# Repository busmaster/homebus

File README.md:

homebus
=======

home automation system

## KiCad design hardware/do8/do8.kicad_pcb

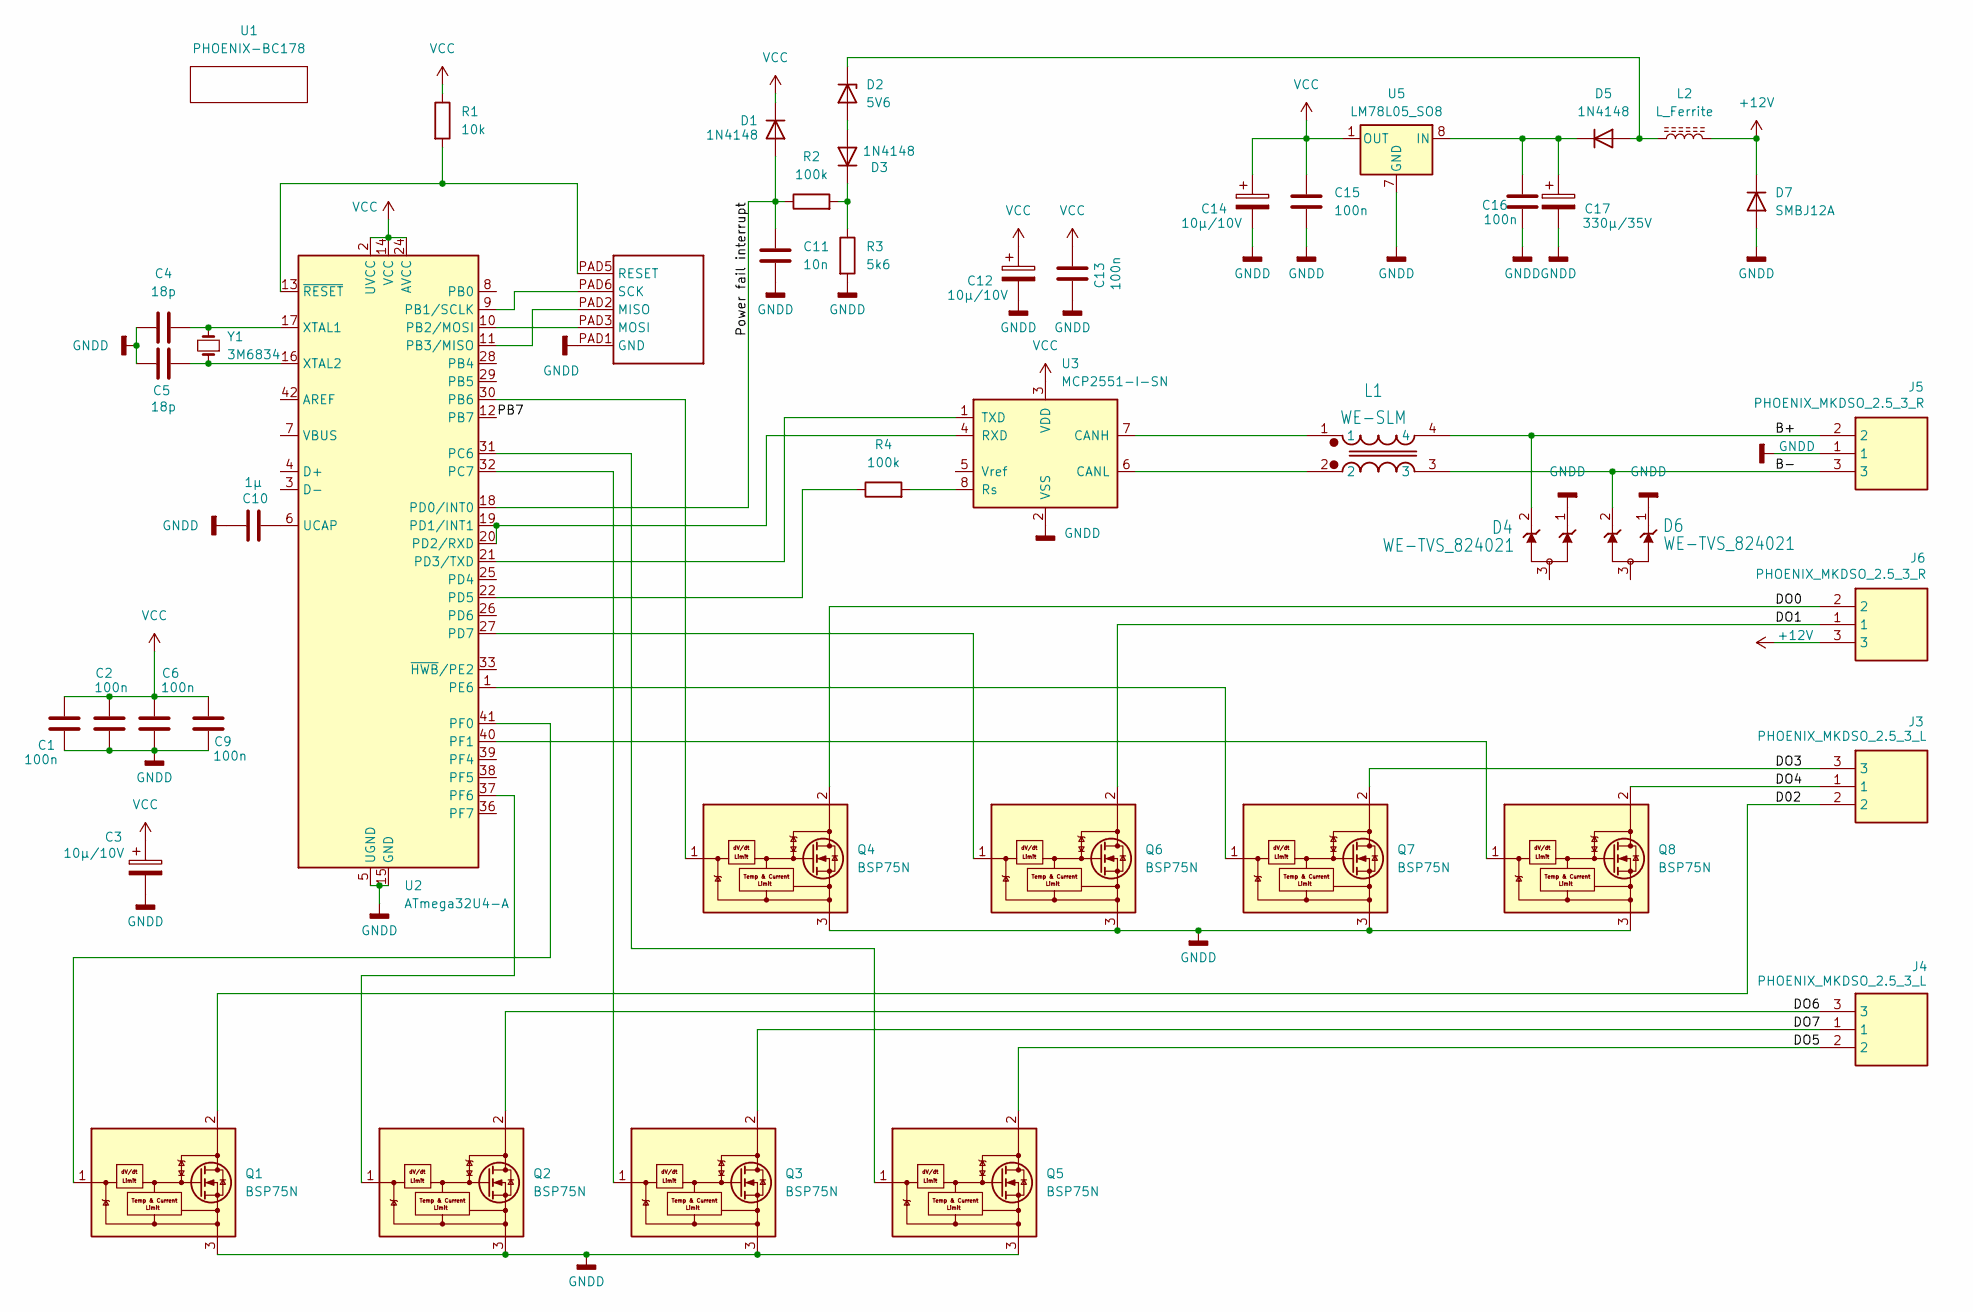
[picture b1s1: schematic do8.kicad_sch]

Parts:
C1, C2, C6, C9, C13, C15, C16: 100n; C_0603_1608Metric_Pad1.08x0.95mm_HandSolder
C3, C12, C14: 10µ/10V; CP_EIA-3216-18_Kemet-A_HandSolder
C4, C5: 18p; C_0603_1608Metric_Pad1.08x0.95mm_HandSolder
C10: 1µ; C_1206_3216Metric_Pad1.33x1.80mm_HandSolder
C11: 10n; C_0603_1608Metric_Pad1.08x0.95mm_HandSolder
C17: 330µ/35V; CP_Elec_10x10.5
D1, D3, D5: 1N4148; D_MiniMELF
D2: 5V6; D_MiniMELF
D4, D6: WE-TVS_824021
D7: SMBJ12A; D_SMB
J3, J4: PHOENIX_MKDSO_2.5_3_L; phoenix_mkdso_2.5_3_l; Manufacturer_Part_Number 2854102; Mouser Part Number 651-2854102
J5, J6: PHOENIX_MKDSO_2.5_3_R; phoenix_mkdso_2.5_3_r; Manufacturer_Part_Number 2854092; Mouser Part Number 651-2854092
L1: WE-SLM
L2: L_Ferrite; L_1806_4516Metric
Q1, Q2, Q3, Q4, Q5, Q6, Q7, Q8: BSP75N; SOT-223
R1: 10k; R_0603_1608Metric_Pad0.98x0.95mm_HandSolder
R2, R4: 100k; R_0603_1608Metric_Pad0.98x0.95mm_HandSolder
R3: 5k6; R_0603_1608Metric_Pad0.98x0.95mm_HandSolder
T1: atmel-isp
U1: PHOENIX-BC178; phoenix-bc178-reduced-3
U2: ATmega32U4-A; TQFP-44_10x10mm_P0.8mm
U3: MCP2551-I-SN; SOIC-8_3.9x4.9mm_P1.27mm
U5: LM78L05_SO8; SOIC-8_3.9x4.9mm_P1.27mm
Y1: 3M6834; Crystal_SMD_HC49-SD

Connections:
+12V: D7.1 (K), J6.3, L2.2
/B+: D4.2, J5.2, L1.4
/B-: D6.2, J5.3, L1.3
/D02: J3.2, Q1.2 (DRAIN)
/DO0: J6.2, Q4.2 (DRAIN)
/DO1: J6.1, Q6.2 (DRAIN)
/DO3: J3.3, Q7.2 (DRAIN)
/DO4: J3.1, Q8.2 (DRAIN)
/DO5: J4.2, Q5.2 (DRAIN)
/DO6: J4.3, Q2.2 (DRAIN)
/DO7: J4.1, Q3.2 (DRAIN)
/Power fail interrupt: C11.1, D1.2 (A), R2.1, U2.18 (PD0)
GNDD: C1.1, C2.1, C3.2, C4.1, C5.1, C6.1, C9.1, C10.2, C11.2, C12.2, C13.1, C14.2, C15.2, C16.2, C17.2, D4.1, D6.1, D7.2 (A), J5.1, Q1.3 (SOURCE), Q1.4 (SOURCE), Q2.3 (SOURCE), Q2.4 (SOURCE), Q3.3 (SOURCE), Q3.4 (SOURCE), Q4.3 (SOURCE), Q4.4 (SOURCE), Q5.3 (SOURCE), Q5.4 (SOURCE), Q6.3 (SOURCE), Q6.4 (SOURCE), Q7.3 (SOURCE), Q7.4 (SOURCE), Q8.3 (SOURCE), Q8.4 (SOURCE), R3.2, T1.PAD1 (GND), U2.5 (UGND), U2.15 (GND), U2.23 (GND), U2.35 (GND), U2.43 (GND), U3.2 (VSS), U5.2 (GND), U5.3 (GND), U5.6 (GND), U5.7 (GND)
unnamed: D2.2 (A), D3.2 (A)
unnamed: D2.1 (K), D5.2 (A), L2.1
unnamed: D3.1 (K), R2.2, R3.1
unnamed: C16.1, C17.1, D5.1 (K), U5.8 (IN)
unnamed: Q1.1 (IN), U2.41 (PF0)
unnamed: Q2.1 (IN), U2.37 (PF6)
unnamed: Q3.1 (IN), U2.32 (PC7)
unnamed: Q4.1 (IN), U2.30 (PB6)
unnamed: Q5.1 (IN), U2.31 (PC6)
unnamed: Q6.1 (IN), U2.27 (PD7)
unnamed: Q7.1 (IN), U2.1 (PE6)
unnamed: Q8.1 (IN), U2.40 (PF1)
unnamed: T1.PAD2 (MISO), U2.11 (PB3)
unnamed: T1.PAD3 (MOSI), U2.10 (PB2)
unnamed: R1.2, T1.PAD5 (RESET), U2.13 (~RESET)
unnamed: T1.PAD6 (SCK), U2.9 (PB1)
unnamed: U2.19 (PD1), U2.20 (PD2), U3.4 (RXD)
unnamed: U2.21 (PD3), U3.1 (TXD)
unnamed: R4.1, U2.22 (PD5)
unnamed: C10.1, U2.6 (UCAP)
unnamed: C4.2, U2.17 (XTAL1), Y1.2
unnamed: C5.2, U2.16 (XTAL2), Y1.1
unnamed: L1.1, U3.7 (CANH)
unnamed: L1.2, U3.6 (CANL)
unnamed: R4.2, U3.8 (Rs)
VCC: C1.2, C2.2, C3.1, C6.2, C9.2, C12.1, C13.2, C14.1, C15.1, D1.1 (K), R1.1, U2.2 (UVCC), U2.14 (VCC), U2.24 (AVCC), U2.34 (VCC), U2.44 (AVCC), U3.3 (VDD), U5.1 (OUT)

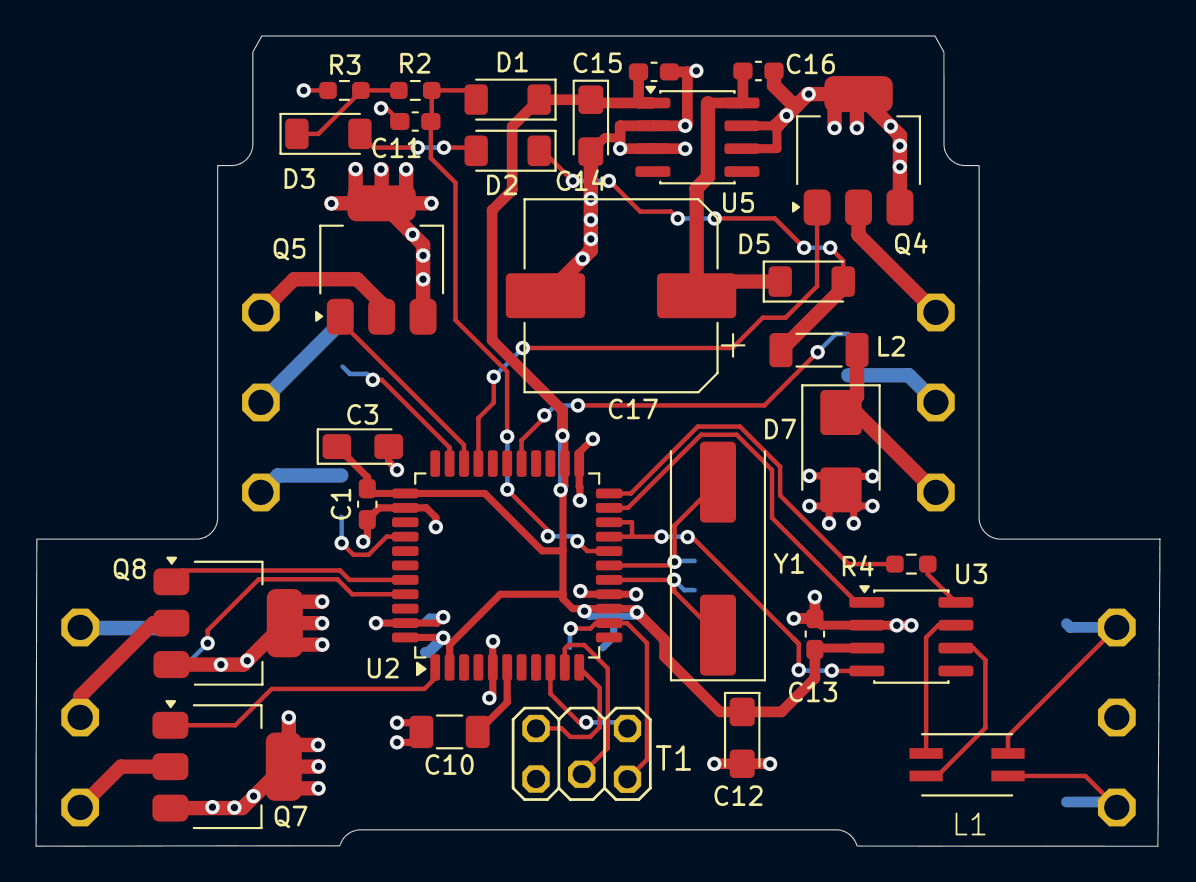
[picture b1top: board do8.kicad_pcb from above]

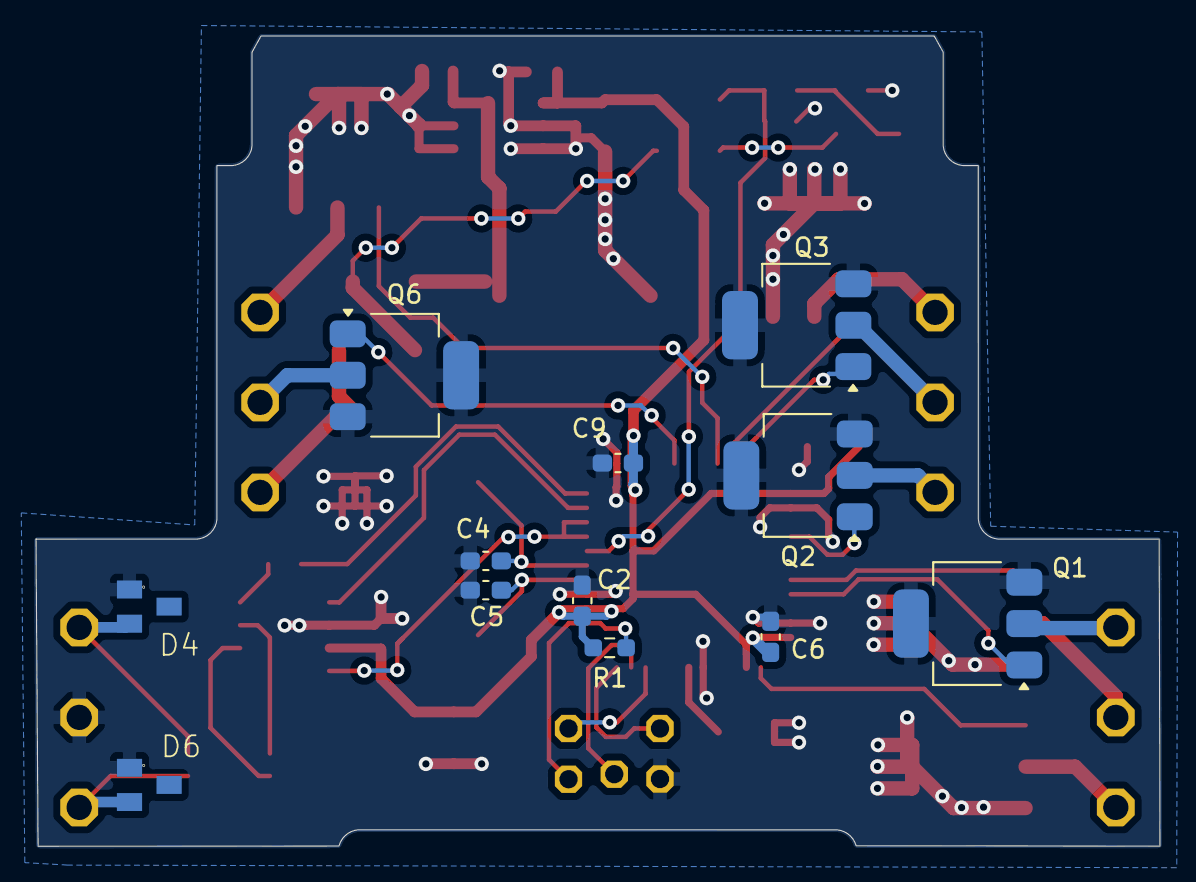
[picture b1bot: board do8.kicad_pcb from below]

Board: 2 copper layers, 62.4 x 45.0 mm, 46 parts (12 on the bottom side), 39 nets.

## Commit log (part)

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2015-11-28 status led integration
2015-11-29 allow client pty while sio device is not yet available
2015-12-01 mega88 clock calibration
2015-12-05 correction of build directory path
2016-01-25 new bus telegram types for clock calibration
2016-01-25 clock calibration
2016-01-25 clock calibraton firmware for atmega88 based devices
2016-02-01 sio send lockup
2016-02-01 change of manufacturer and product string
2016-02-09 sio driver reports one received character on startup
2016-02-09 file mode changes
2016-02-11 Update README
    Test2
2016-02-19 elko position move
2016-02-23 bootloader for rs485if
2016-02-25 Fix usage message in eventmonitor and monitor
2016-02-29 firmwareupdate doesn't start due to buffered rx frames in sio device
2016-02-29 adapt file mode
2016-02-29 remove debug sio support
2016-02-29 prepare usage of siosingle
2016-03-08 removed bit offset undefs for m128 (moved to sio_c.h)
2016-03-08 version 1.05 (use of siosingle)
2016-03-08 use of siosingle for switchv2
2016-03-08 preparation for siosingle usage at do31 and rs485if
2016-03-13 board specific modules for rs485if
2016-03-15 atmega1284 adaptions
2016-03-19 dmx test
2016-03-19 correction of BUS_TRANSCEIVER_POWER_UP macro
2016-03-19 part value actualization
2016-03-19 set unix line termination
2016-03-20 port settings
2016-04-10 doc for initial flash setup
2016-04-10 correction of programming steps
2016-05-09 change actval from max wind to current wind
2016-05-16 auto switch off for lamp in garage and bathroom
2016-05-30 read command from stdin to terminate process
2016-05-30 correction of select rfds setup
2016-06-27 New window for kitchen. Support addition kitchen lamp.
2016-06-27 new window for kitchen
2016-09-18 change of socket_1 relais connection from NO to NC
2016-09-18 add support for 14.7456MHz and 1.8432MHz clock
2016-09-18 hardware design pwm4
2016-09-19 new command: generate a switch event
2016-09-21 set default own address in server mode
2016-09-21 set default own address in server mode to command line parameter
2016-09-21 converted to unix line termination
2016-09-21 setup window for disabling the doorbell
2016-10-01 changed crystal frequency
2016-10-01 add support for rs485if and pwm4 devices
2016-10-03 initial version of pwm4 application
2016-10-03 missing file
2016-10-03 rs485 test
2016-10-03 support for rs485f and pwm4
2016-10-10 reduce flash usage by sio tx simplification
2016-10-15 support rs485if and pwm4 actval
2016-10-15 optocoupler input and output resistor change
2016-10-17 output restore on power on
2016-10-17 unix line termination
2016-10-17 pwm for switch 46
2016-10-25 new command inforange for bus scan
2016-10-30 enable pullup on all input pins
2016-12-14 missing header
2017-01-03 save max wind value to eeprom
2017-01-03 rearrangement of buttons
2017-01-03 file mode
2017-01-04 sleep before flushing the sio input on startup
2017-01-17 use siosingle
2017-01-31 pwm4: set pwm frequency to 900 Hz from 225 Hz
    This high frequency is required due to instability of the used power supply
    (Meanwell LRS-50-24).
2017-01-31 pwm4 sio: support for additional cpu clocks
2017-02-18 eventmonitor: support device type PWM4
2017-02-27 removed debug print
2017-02-28 pwm: extension of interface: separate function for on/off
2017-02-28 sio: support EVEN parity
2017-02-28 pwm4 application: use extended pwm interface
2017-02-28 smartmeter tool: use EVEN parity
2017-02-28 new hardware: smartmeter interface
2017-03-14 smartmeterif: initial debug version
2017-03-18 smartmeter support
2017-03-18 pwm4: renaming mask -> set
2017-03-19 add new telegram type for diag data
2017-03-19 monitor: add support for diag telegram
2017-04-04 pwm4 application: delayed switch off of the common power supply
2017-04-04 smartmeterif hardware: value changes
2017-05-07 change \r\n to \n
2017-05-07 fflush stdout
2017-05-09 visu: reduce code duplication
2017-05-13 modulservice: check receiver address
2017-05-24 tools: mqtt: initial demo version
2017-06-04 mqtt: test
2017-06-04 tools: mqtt: pasre command line params
2017-06-05 tools: eventmonitor: optional listen only mode
2017-06-05 tools: mqtt: parameter for event listen address
2017-06-05 do31: eBusDevReqSetClientAddr does not work
2017-06-19 pwm4: unable to switch on after power fail
2017-06-20 tools: mqtt: subscriber support for do31 shader
2017-07-02 tools: mqtt: command line parameter for broker address/port
2017-07-02 tools: mqtt: debian init script example
2017-07-11 tools: mqtt: wait for response on DO31 ReqSetValue
2017-07-11 usbif: use siosingle
2017-07-15 tools: bottongpio: initial version
2017-07-15 tools: buttongpio: wrong telegram processing
2017-07-16 tool: mqtt: extend example configuration
2017-07-22 tools: mqtt: add lights stairs
2017-07-25 tools: modulservice: support changed pwm4 actval protocol
2017-07-25 pwm4: wrong actval state
2017-07-29 tools: mqtt: add PWM4 support
2017-08-09 tools: mqtt: sw8 device support
2017-10-17 buttongpio: trigger on swtichstate additionally
2017-10-31 switchv2a: replace switchState by actualValue telegrams
2017-10-31 project241: use eDigOut30 for door light
2017-11-07 bus: introduction gettime/settime telegram types
2017-11-11 application240: door light auto/on/off
2017-11-11 mqtt: topic extension
2017-11-12 buttongpio: add supoort for eBusDevReqActualValueEvent/sw8 telegram
2017-11-20 visu: implement ButtonBackPressed to call dialog's hide methode
2017-11-20 visu: support mjpeg camera
2017-11-26 visu: auto mode for door light
2017-11-27 visu: remove moduleservice debug prints
2017-11-28 visu: smartmeter support
2017-12-05 added .gitignore
2017-12-05 visu: do not smartmeter from startup
2017-12-11 add missing files
2017-12-11 add hardware
2018-02-24 monitor: support eBusDevTypeSmIf
2018-02-24 change to unix line ending
2018-02-25 switchv2_garage: optimize for size
2018-02-25 switchv2_luminance: optimize for size
2018-02-25 monitor: add setvar/getvar support
2018-02-25 monitor: output format cleanup
2018-04-03 bus: busvar support
2018-04-03 monitor: use variable for compiler options
2018-04-03 monitor: add setvar/getvar result code
2018-04-07 busvar: change index type to uint8_t from uint16_t
2018-04-08 monitor: wrong usage help for option logfile
2018-05-12 busvar: stabilisation
2018-06-26 busvar: make variable value peristent to eeprom optionally
2018-06-26 klaus240: use siosingle
2018-07-28 tools: initial varserver
2018-09-22 bustest: correction of library dependency order
2018-10-08 bus: pwm16 protocol support
2019-01-19 sonoff_socket: initial version
2019-10-30 sw88 1.06 hAT
2019-10-30 Anpassungen
2019-10-30 gitignore
2019-10-30 Hardwarelayouts
2019-10-30 Bootloader
2019-10-30 pwm16
2019-10-30 Projekt hinzugefügt
2019-10-30 missing makefile
2019-10-30 Eagle Files pwm16 added
2019-11-01 Portserver für Webapp
2019-11-07 spelling error
2019-11-08 tasttimeout
2019-11-25 do31: set reset state of interrupt mask registers
    The bootloader might leave interrupt mask register settings that
    can trigger unexcepted interrupts. These unexpected interrupt are
    handled by the default handler that calls the reset handler.
2020-05-03 mqtt: support sw8 input actval event
    On publishing mqtt sw8 input events a bus actval event is generated:
    mosq_publish ... -t home/eingang/bewegungsmelder/set -m 1
    -> bus actval event to all receivers from the configuration receiver option
    -> mqtt publish home/eingang/bewegungsmelder/actual
    The configuration has to be extended by the receiver option, e.g.:
    - topic: home/eingang/bewegungsmelder
2020-05-24 busvar: whitespace cleanup
2020-05-29 mqtt: add bus variable support
    bus device sends ReqSetVar to mqtt -> publish variable actual value
    publish variable set value to mqtt -> ReqSetVar to bus device
    To enable subscribtion to bus variables the bus device has to send ReqSetVar
    to mqtt virtual bus device.
2020-05-31 monitor: fix line feed output of RespSetVar
2020-05-31 visu: use new creator
2020-06-09 mqtt: publish var directly on var subscription callback
    Before publish var was triggered by bus ReqSetVar only.
2020-06-11 mqtt: do not publish retained
2020-06-11 mqtt: undo disable retained messages
2020-06-14 mqtt: support DO31 active low outputs
2020-06-14 mqtt: rename variable topic in example config
2020-06-19 visu: replace the proprietary device access with mqtt
2020-06-21 visu: remove unused variable
2020-06-23 klaus240: use bus variables for bell mode and door light mode
2020-07-03 bus: extend ActualValueEvent by smif
2020-07-03 smif: add ActualValueEvent for smartmeter data
    The ActualValueEvent is enabled by setting bus variable 0 to 1.
    After N seconds bus variable 0 is reset automatically. N is read from
    bus variable 1. The receiver address of the ActualValueEvent is read from
    bus varibale 2.
2020-07-04 smif: fix message type for ActualValueEvent
2020-07-04 monitor: add supoort for smif ActualValueEvent
2020-07-04 visu: support smartmeter
2020-07-09 bus: save firmware from device to file
2020-07-09 tools: add firmwaresave
2020-07-09 monitor: support firmware save protocol extension
2020-07-10 smif: support reading of firmware flash image
2020-07-11 smif: force a ActualValueEvent on enabling it
2020-07-11 pwm4: support reading of firmware flash image
2020-07-14 firmwaresave: fix compiler warning
2020-07-17 mqtt: do not call BusCheck multiple times in main loop
    When BusCheck is called it consumes the last packet from the receive queue.
    So serve_bus was disabled to get all packet from bus and some publish messages
    were missing sporadically.
2020-07-21 bus: change file attributes
2020-07-23 mqtt: publish actual value of bbusvar on bus response
2020-07-23 visu: use QHash to match compare strings
2020-07-25 visu: auto reconnect to mqtt broker
2020-07-26 sonoff_socket: remove startup mqtt message
2020-08-06 visu: adapt to 800x480 resolution
2020-08-06 visu: generalize device support
    hwmon devices are searched by name.
2021-05-15 mqtt: disable logging of stdout to syslog
2021-07-10 Add keyboard device
2021-07-28 hardware: smartmeterif: Add png
2021-08-23 Integrate support for ABUS CFA3100
    CFA3100 is controlled by CFF3100 bluetooth remote control. Bus access to CFF3100 is implemented by
    cff3100if device. For user code input a keypad is used.
    Use case:
    1) User enters code at the keypad
    2) The keypad bus device, based on switchv2 hardware, sends the key codes entered to the
    cff3100if device
2021-08-28 cff3100if: Read lock state
2021-08-28 hardware: cff3100if: Beautify schematic
2021-08-29 cff3100if: Add setvalue
2021-08-30 cff3100if: Fix key code handling
2021-09-25 tools: mqtt: Support keyrc
2021-10-25 cff3100if: Send response at end of state sequence
    The bus response was sent but while the lock state machine was in
    termination state, no further requests were accepted.
2021-11-28 stoveguard: initial fw version
2021-12-08 stoveguard: Add initial hardware revision
2022-03-25 visu: Change to chunked mjpg transfer encoding
    Required due to camera update to Debian 11.
2022-05-01 keyrc: Add key code for eBusButtonPressedX telegram
2022-05-01 klaus240: Add function for switching 'Licht Eingang' manually
2022-07-09 hardware/smartmeterif: Board version 2
    - voltage regulator housing collision
    - size reduction
2022-07-30 visu: Add smartmeter data
2023-04-16 visu: Add PV data
2023-04-17 visu: Show current power
2023-08-27 visu: Remove P+ and P-
2023-09-17 visu: Separate meter/pv, doorlocker and io events
    doorlocker state shall not be updated by meter/pv or io events.
2023-12-15 stoveguard: Send output event to clients
2023-12-15 monitor: Add support for stoveguard
2024-05-02 hardware: Add usbif schematics png
2026-01-02 visu: Fix mjpeg processing
    A completed jpeg image might be contained in a single http chunk.
2026-01-06 Tools: portserver: Add systemd install example
2026-01-18 DO31 sio: undef U2X
    Wrong UART baud rate at mega128@1MHz. Double baud rate not working.
2026-01-18 DO31 bootloader: Add readme for device setup
2026-01-18 DO31 bootloader: Remove AVRStudio project file
2026-01-18 DO31 bootloader: Add bootloader for devices using 1MHz MCU clock
2026-01-18 makefile: avr-size: Remove unsupport option -C
    Newer versions don't support -C anymore.
2026-01-25 Add projects DO31 Kurt
2026-03-08 Tools: mqtt: Fix typo
2026-04-27 visu: Display storage data
2026-05-01 visu: Adapt smartmeter window geometry
2026-06-21 Ordered PCB
